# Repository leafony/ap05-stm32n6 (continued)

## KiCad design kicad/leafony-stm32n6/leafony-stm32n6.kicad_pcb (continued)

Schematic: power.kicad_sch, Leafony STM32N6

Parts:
C56, C61, C63, C64, C65, C66: 10uF(M) 10V X7R; C_0603_1608Metric
C57, C58: 4.7uF(M) 6.3V X7R; C_0603_1608Metric
C59, C60, C62, C67, C68, C69, C70: 1uF(M) 50V X5R; C_0402_1005Metric
L4, L5: 0.47uH; IND_DFE201610E_MUR
R70, R71, R72, R73, R74, R75: 0R 1/4W; R_0603_1608Metric
TP2, TP3, TP4, TP5, TP6, TP7: TestPoint; TestPoint_Pad_D1.0mm
U11: LD56100DPU18R; DFN8_1P6X1P2X0P4_STM
U12: TPS6282518DMQR; DMQ0006A
U13: TPS6282533DMQR; DMQ0006A
U14: LD39020ADTPU18R; VREG_LD39020ADTPU18R; PARTREV 5
U15: LD39020ADTPU33R; VREG_LD39020ADTPU33R; PARTREV 5
U16: MAX40200ANS; WLP-4_0.728x0.728mm_Layout2x2_P0.35mm

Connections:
+3V3: R74.2, TP6.1; also elsewhere on the board
+5V: C57.1, C58.1, C59.1, C67.1, U12.6 (VIN), U13.6 (VIN), U14.3 (EN), U14.4 (IN), U15.3 (EN), U15.4 (IN); also elsewhere on the board
GND: C56.2, C57.2, C58.2, C59.2, C60.2, C61.2, C62.2, C63.2, C64.2, C65.2, C66.2, C67.2, C68.2, C69.2, C70.2, U11.3 (LCON), U11.5 (GND), U11.9 (EPAD), U12.4 (GND), U13.4 (GND), U14.2 (GND), U14.5 (GND__1), U15.2 (GND), U15.5 (GND__1), U16.B2 (GND); also elsewhere on the board
unnamed: C64.1, R71.1, U11.1 (VOUT), U11.2 (VOUT), U11.4 (FB)
unnamed: C61.1, C65.1, L4.2, R72.1, U12.3 (FB)
unnamed: L4.1, U12.5 (SW)
unnamed: C63.1, C66.1, L5.2, R73.1, U13.3 (FB)
unnamed: L5.1, U13.5 (SW)
unnamed: C60.1, C62.1, R70.1, U14.1 (OUT)
unnamed: C69.1, C70.1, R75.1, U15.1 (OUT)
unnamed: R74.1, U16.A2 (OUT)
PWR_ON: U11.6 (EN), U12.1 (EN), U13.1 (EN); also elsewhere on the board
VDD1V8: R72.2, TP4.1; also elsewhere on the board
VDD3V3: C56.1, C68.1, R73.2, TP5.1, U11.7 (VIN), U11.8 (VIN), U16.A1 (VDD), U16.B1 (EN); also elsewhere on the board
VDDA1V8: R71.2, TP3.1; also elsewhere on the board
VDDA1V8_AON: R70.2, TP2.1; also elsewhere on the board
VDDIO: R75.2, TP7.1; also elsewhere on the board

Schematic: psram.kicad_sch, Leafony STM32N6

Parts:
C42, C43: 100nF(M) 16V X7R; C_0201_0603Metric
C44, C45: 4.7uF(M) 16V X5R; C_0603_1608Metric
R57: 10k(J); R_0402_1005Metric
R58: 0R 1/4W; R_0603_1608Metric
U3: APS256XXN-OBR-BG; BGA24C100P5X5_800X600X120; PARTREV 1.00

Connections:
GND: C42.1, C43.1, C44.1, C45.1, U3.C1 (VSS), U3.E5 (VSS); also elsewhere on the board
HEXASPI_CLK: U3.B2 (CLK); also elsewhere on the board
HEXASPI_DSQ0: U3.C3 (DQS/DM0); also elsewhere on the board
HEXASPI_DSQ1: U3.B3 (DQS/DM1); also elsewhere on the board
HEXASPI_IO0: U3.D3 (ADQ0); also elsewhere on the board
HEXASPI_IO1: U3.D2 (ADQ1); also elsewhere on the board
HEXASPI_IO2: U3.C4 (ADQ2); also elsewhere on the board
HEXASPI_IO3: U3.D4 (ADQ3); also elsewhere on the board
HEXASPI_IO4: U3.D5 (ADQ4); also elsewhere on the board
HEXASPI_IO5: U3.E3 (ADQ5); also elsewhere on the board
HEXASPI_IO6: U3.E2 (ADQ6); also elsewhere on the board
HEXASPI_IO7: U3.E1 (ADQ7); also elsewhere on the board
HEXASPI_IO8: U3.C2 (DQ8); also elsewhere on the board
HEXASPI_IO9: U3.B1 (DQ9); also elsewhere on the board
HEXASPI_IO10: U3.A2 (DQ10); also elsewhere on the board
HEXASPI_IO11: U3.A4 (DQ11); also elsewhere on the board
HEXASPI_IO12: U3.A5 (DQ12); also elsewhere on the board
HEXASPI_IO13: U3.B4 (DQ13); also elsewhere on the board
HEXASPI_IO14: U3.B5 (DQ14); also elsewhere on the board
HEXASPI_IO15: U3.C5 (DQ15); also elsewhere on the board
HEXASPI_NCS: R57.2, U3.A3 (~CE); also elsewhere on the board
VDDA1V8: R58.1; also elsewhere on the board
VDD_HEXASPI_M: C42.2, C43.2, C44.2, C45.2, R57.1, R58.2, U3.D1 (VDD), U3.E4 (VDD)

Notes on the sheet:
Place close to each VDD/VSS pair.

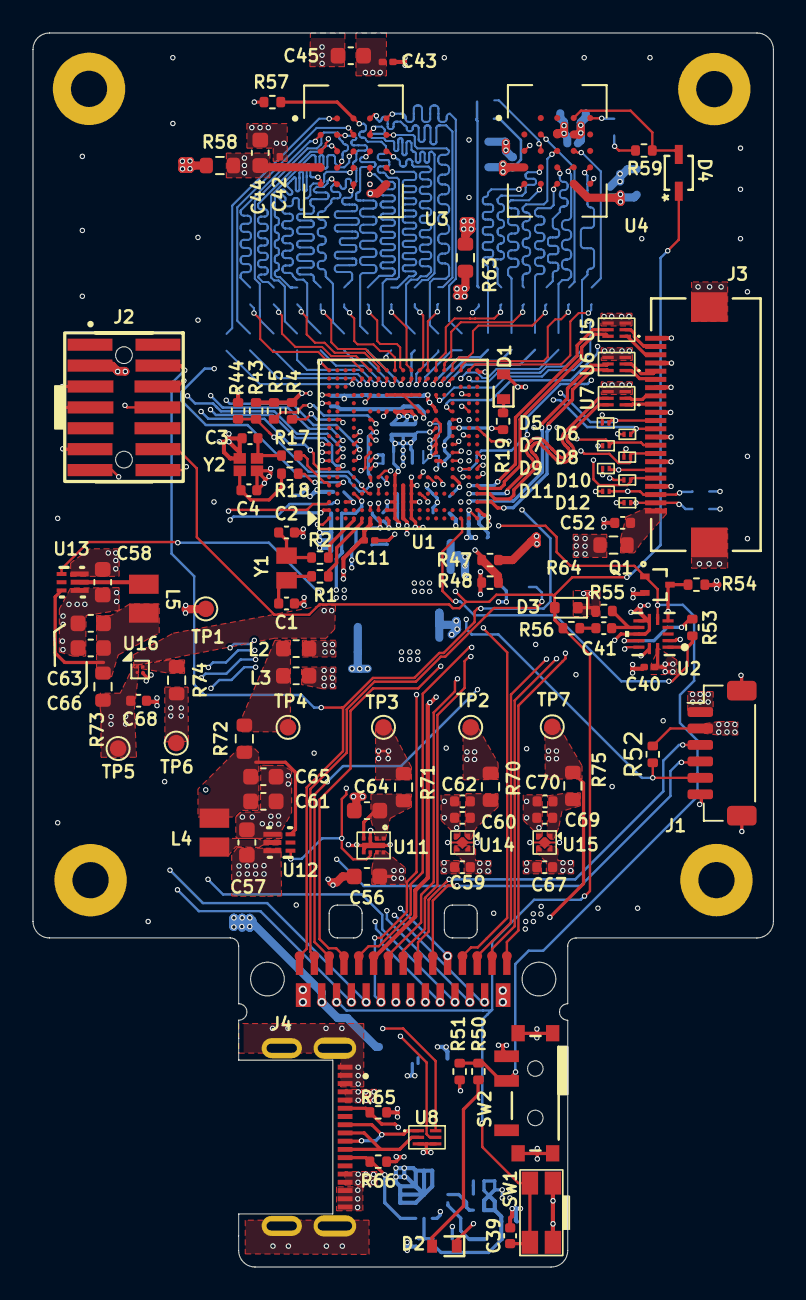
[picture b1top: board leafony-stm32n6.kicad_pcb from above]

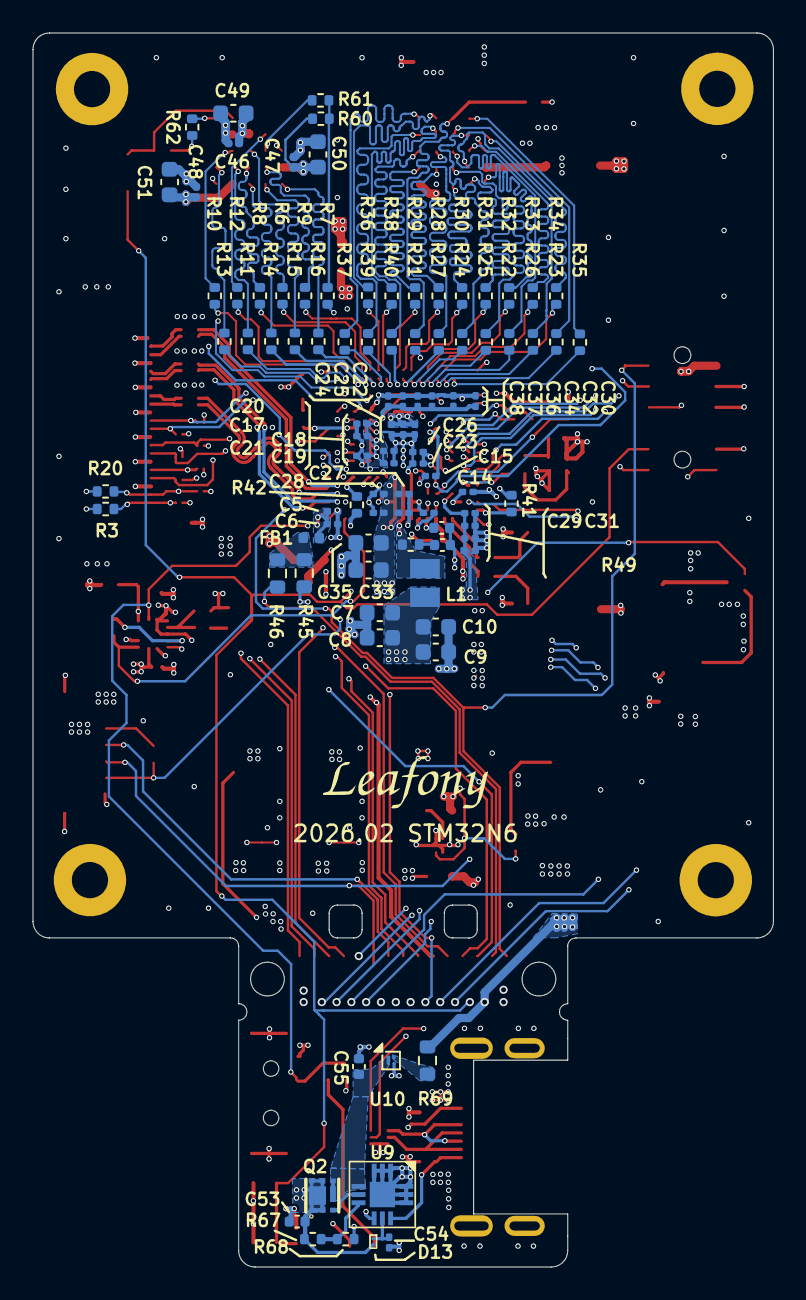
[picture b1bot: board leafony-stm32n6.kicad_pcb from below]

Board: 6 copper layers, 45.0 x 75.0 mm, 206 parts (96 on the bottom side), 176 nets.

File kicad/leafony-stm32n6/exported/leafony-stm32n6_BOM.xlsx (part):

Reference | Value | Datasheet | Footprint | Qty | DNP | 説明 | MANUFACTURER | Model No
C1,C2 | 3.3pF(J) 50V C0G | https://www.yageo.com/en/Chart/Download/pdf/CC0402BRNPO9BN3R3 | Capacitor_SMD:C_0402_1005Metric | 2 |  | 3.3 pF ±0.1pF 50V セラミックコンデンサ C0G、NP0 0402（1005メートル法） | Yageo | CC0402BRNPO9BN3R3
C3,C4 | 8.2pF(J) 50V C0G | https://www.yageo.com/en/Chart/Download/pdf/CC0402CRNPO9BN8R2 | Capacitor_SMD:C_0402_1005Metric | 2 |  | 8.2 pF ±0.25pF 50V セラミックコンデンサ C0G、NP0 0402（1005メートル法） | Yageo | CC0402CRNPO9BN8R2
C5,C14,C17-C21,C29,C31 | 1uF(M) 6.3V X5R | https://search.murata.co.jp/Ceramy/image/img/A01X/G101/ENG/G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 | Capacitor_SMD:C_0201_0603Metric | 9 |  | 1 µF ±20% 6.3V セラミックコンデンサ X5R 0201（0603メートル法） | Murata Electronics | GRM033R60J105MEA2
C6,C11,C15,C16,C22-C28,C30,C32,C34,C36-C38,C40,C42,C43,C46-C48,C54,C71-C74 | 100nF(M) 16V X7R | https://search.murata.co.jp/Ceramy/image/img/A01X/G101/ENG/G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 | Capacitor_SMD:C_0201_0603Metric | 28 |  | 0.1 µF ±10% 16V セラミックコンデンサ X7S 0201（0603メートル法） | Murata Electronics | GRM033C71C104KE14D
C7-C10 | 22uF(M) 6.3V X5R | https://search.murata.co.jp/Ceramy/image/img/A01X/G101/ENG/G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 | Capacitor_SMD:C_0603_1608Metric | 4 |  | 22 µF ±20% 6.3V セラミックコンデンサ X5R 0603（1608メートル法） | Murata Electronics | GRM188R60J226MEA0J
C12 | 4.7uF(M) 10V X5R | https://search.murata.co.jp/Ceramy/image/img/A01X/G101/ENG/G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 | Capacitor_SMD:C_0402_1005Metric | 1 |  | 4.7 µF ±20% 10V セラミックコンデンサ X5R 0402（1005メートル法） | Murata Electronics | GRM155R61A475MEAAD
C13 | 2.2nF(M) 50V X7R | https://www.yageogroup.com/content/datasheet/asset/file/UPY-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 | Capacitor_SMD:C_0402_1005Metric | 1 |  | 2200 pF ±10% 50V セラミックコンデンサ X7R 0402（1005メートル法） | Yageo | CC0402KRX7R9BB222
C33,C35,C56,C61,C63-C66 | 10uF(M) 10V X7R | https://search.murata.co.jp/Ceramy/image/img/A01X/G101/ENG/G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 | Capacitor_SMD:C_0603_1608Metric | 8 |  | 10 µF ±20% 10V セラミックコンデンサ X7R 0603（1608メートル法） | Murata Electronics | GRM188Z71A106MA73D
C39,C53 | 10nF(M) 50V X7R | https://search.murata.co.jp/Ceramy/image/img/A01X/G101/ENG/G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 | Capacitor_SMD:C_0402_1005Metric | 2 |  | 10000 pF ±10% 50V セラミックコンデンサ X7R 0402（1005メートル法） | Murata Electronics | GRM155R71H103KA88D
C41 | 0.47uF(M) 6.3V X5R | https://search.murata.co.jp/Ceramy/image/img/A01X/G101/ENG/G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 | Capacitor_SMD:C_0402_1005Metric | 1 |  | 0.47 µF ±10% 6.3V セラミックコンデンサ X5R 0402（1005メートル法） | Murata Electronics | GRM155R60J474KE19D
C44,C45,C49-C51 | 4.7uF(M) 16V X5R | https://www.yageogroup.com/content/datasheet/asset/file/UPY-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 | Capacitor_SMD:C_0603_1608Metric | 5 |  | 4.7 µF ±10% 16V セラミックコンデンサ X5R 0603（1608メートル法） | Yageo | CC0603KRX5R7BB475
C52,C55,C59,C60,C62,C67-C70 | 1uF(M) 50V X5R | https://search.murata.co.jp/Ceramy/image/img/A01X/G101/ENG/G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 | Capacitor_SMD:C_0402_1005Metric | 9 |  | 1 µF ±20% 50V セラミックコンデンサ X5R 0402（1005メートル法） | Murata Electronics | GRM155R61H105ME05D
C57,C58 | 4.7uF(M) 6.3V X7R | https://mm.digikey.com/Volume0/opasdata/d220001/medias/docus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 | Capacitor_SMD:C_0603_1608Metric | 2 |  | 4.7 µF ±20% 6.3V セラミックコンデンサ X7R 0603（1608メートル法） | Taiyo Yuden | JMK107BB7475MA-T
CN1 | Leafony Bus | https://docs.leafony.com/ | Leafony:CN_F29 | 1 |  | Leafony Bus | Leafony Systems Inc. | Leafony Bus
D1,D2 | SML-A12U8TT86 | https://www.rohm.co.jp/datasheet?p=SML-A12U8T&dist=Digi-key&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 | Leafony:LED_SML-A12_ROM | 2 |  | 赤 620nm LED表示 - ディスクリート 2.2V 2-SMD、リードなし | Rohm Semiconductor | SML-A12U8TT86
D3 | 1SS387 | https://mm.digikey.com/Volume0/opasdata/d220001/medias/docus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 | Diode_SMD:D_SOD-523 | 1 |  | DIODE GEN PURP 80V 100MA ESC | Toshiba Semiconductor and Storage | 1SS387
D4 | BAT60JFILM | https://www.st.com/resource/en/datasheet/bat60.pdf | Leafony:CR_60JFILM_STM | 1 |  | DIODE SCHOTTKY 10V 3A SOD323 | STMicroelectronics | BAT60JFILM
D5-D12 | DF2S7MSL,L3F | https://toshiba.semicon-storage.com/info/docget.jsp?did=3071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 | Leafony:SOD-962 SL2_TOS | 8 |  | TVS DIODE 5VWM 20VC SL2 | Toshiba Semiconductor and Storage | DF2S7MSL,L3F
D13 | BAT30F4 | https://www.st.com/content/ccc/resource/technical/document/d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 | Leafony:CR_B30F4_STM | 1 |  | DIODE SCHOTTKY 30V 300MA 0201 | STMicroelectronics | BAT30F4
FB1 | MPZ1005S300CT000 | https://product.tdk.com/info/ja/catalog/datasheets/beads_com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 | Fuse:Fuse_0402_1005Metric | 1 |  | FERRITE BEAD 30 OHM 0402 1LN | TDK Corporation | MPZ1005S300CT000
J1 | BM06B-SRSS-TB | https://www.jst-mfg.com/product/pdf/eng/eSH.pdf | Connector_JST:JST_SH_BM06B-SRSS-TB_1x06-1MP_P1.00mm_Vertical | 1 |  | CONN HEADER SMD 6POS 1MM | JST Sales America Inc. | BM06B-SRSS-TB
J2 | FTSH-107-01-L-DV-K-A | https://suddendocs.samtec.com/catalog_english/ftsh_smt.pdf | Leafony:SAMTEC_FTSH-107-01-L-DV-K-A | 1 |  | CONN HEADER SMD 14POS 1.27MM | Samtec | FTSH-107-01-L-DV-K-A
J3 | FH12-22S-0.5SH55 | https://www.hirose.com/product/document?clcode=&productname=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 | Leafony:CONN_FH12-22S-0.5SH55_HIR | 1 |  | 22 極 FFC、FPC コネクタ 端子、下 0.020インチ（0.50mm） 面実装、ライトアングル | Hirose | FH12-22S-0.5SH55
J4 | CX90M-16P | https://www.hirose.com/product/document?clcode=CL0480-0522-0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 | Leafony:HRS_CX90M-16P | 1 |  | CONN RCP USB3.2 TYP C 24P BRD ED | Hirose | CX90M-16P
L1 | 1.0uH | https://search.murata.co.jp/Ceramy/image/img/P02/J(E)TE243A-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 | Leafony:IND_DFE201610E_MUR | 1 |  | 1 µH シールド付き ドラムコア、巻線型 インダクタ 2.2 A 最大60ミリオーム 0806（2016メートル法） | Murata Electronics | DFE201612PD-1R0M=P2
L2 | 18R@100MHz | https://mm.digikey.com/Volume0/opasdata/d220001/medias/docus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 | Inductor_SMD:L_0603_1608Metric | 1 |  | 18 Ohms @ 100 MHz 1 電源ライン フェライトビーズおよびチップ 0603（1608メートル法） 7.5A 4ミリオーム | Taiyo Yuden | LSMCA160808T180NGR
L3 | 2.2nH | https://search.murata.co.jp/Ceramy/image/img/P02/JELF243A-0026.pdf | Inductor_SMD:L_0603_1608Metric | 1 |  | FIXED IND 2.2NH 1.4A 0.018OHM SM | Murata Electronics | LQW18AN2N2D10D
L4,L5 | 0.47uH | https://search.murata.co.jp/Ceramy/image/img/P02/J(E)TE243A-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 | Leafony:IND_DFE201610E_MUR | 2 |  | 470 nH シールド付き ドラムコア、巻線型 インダクタ 3.6 A 最大32ミリオーム 0806（2016メートル法） | Murata Electronics | DFE201610E-R47M=P2
Q1 | RE1C002UNTCL | https://www.rohm.co.jp/datasheet?p=RE1C002UN&dist=Digi-key&m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 | Leafony:DIO_RB558WMF_ROM | 1 |  | MOSFET N-CH 20V 200MA EMT3F | Rohm Semiconductor | RE1C002UNTCL
Q2 | STL6N3LLH6 | https://www.st.com/resource/en/datasheet/stl6n3llh6.pdf | Leafony:POWERFLAT-2X2 | 1 |  | N-channel 30 V, 0.021 typ., 6 A STripFET H6 Power MOSFET in a PowerFLAT 2x2 pac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 | STMicroelectronics | STL6N3LLH6
R1,R2,R6-R18,R21-R40,R48,R56,R61 | 0R | https://www.yageogroup.com/content/datasheet/asset/file/PYU-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 | Resistor_SMD:R_0402_1005Metric | 38 |  | 0 Ohms ジャンパ チップ抵抗 0402（1005メートル法） 耐湿性 厚膜 | Yageo | RC0402JR-070RL
R3-R5,R20 | 4.7k(J) | https://www.yageogroup.com/content/datasheet/asset/file/PYU-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 | Resistor_SMD:R_0402_1005Metric | 4 |  | 4.7 kOhms ±5% 0.063W、1/16W チップ抵抗 0402（1005メートル法） 耐湿性 厚膜 | Yageo | RC0402JR-074K7L
R19,R50 | 1k(J) | https://www.yageogroup.com/content/datasheet/asset/file/PYU-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 | Resistor_SMD:R_0402_1005Metric | 2 |  | RES 1K OHM 5% 1/16W 0402 | Yageo | RC0402JR-071KL
R41,R42 | 200R(F) | https://www.yageogroup.com/content/datasheet/asset/file/PYU-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 | Resistor_SMD:R_0402_1005Metric | 2 |  | 200 Ohms ±1% 0.063W、1/16W チップ抵抗 0402（1005メートル法） 耐湿性 厚膜 | Yageo | RC0402FR-07200RL
R43 | 10k(J) | https://www.yageogroup.com/content/datasheet/asset/file/PYU-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 | Resistor_SMD:R_0402_1005Metric | 1 | DNP | 10 kOhms ±5% 0.063W、1/16W チップ抵抗 0402（1005メートル法） 耐湿性 厚膜 | Yageo | RC0402JR-0710KL
R44,R51,R54,R57,R59,R60,R62 | 10k(J) | https://www.yageogroup.com/content/datasheet/asset/file/PYU-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 | Resistor_SMD:R_0402_1005Metric | 7 |  | 10 kOhms ±5% 0.063W、1/16W チップ抵抗 0402（1005メートル法） 耐湿性 厚膜 | Yageo | RC0402JR-0710KL
R45,R58,R63,R64,R69-R75 | 0R 1/4W | https://www.rohm.co.jp/datasheet?p=PMR03EZPJ000&dist=Digi-Ke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 | Resistor_SMD:R_0603_1608Metric | 11 |  | 0 Ohms ジャンパ チップ抵抗 0603（1608メートル法） 車載用AEC-Q200、ジャンパ 金属素子 | ROHM | PMR03EZPJ000
R46 | 0R 1/4W | https://www.rohm.co.jp/datasheet?p=PMR03EZPJ000&dist=Digi-Ke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 | Resistor_SMD:R_0603_1608Metric | 1 | DNP | 0 Ohms ジャンパ チップ抵抗 0603（1608メートル法） 車載用AEC-Q200、ジャンパ 金属素子 | ROHM | PMR03EZPJ000
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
